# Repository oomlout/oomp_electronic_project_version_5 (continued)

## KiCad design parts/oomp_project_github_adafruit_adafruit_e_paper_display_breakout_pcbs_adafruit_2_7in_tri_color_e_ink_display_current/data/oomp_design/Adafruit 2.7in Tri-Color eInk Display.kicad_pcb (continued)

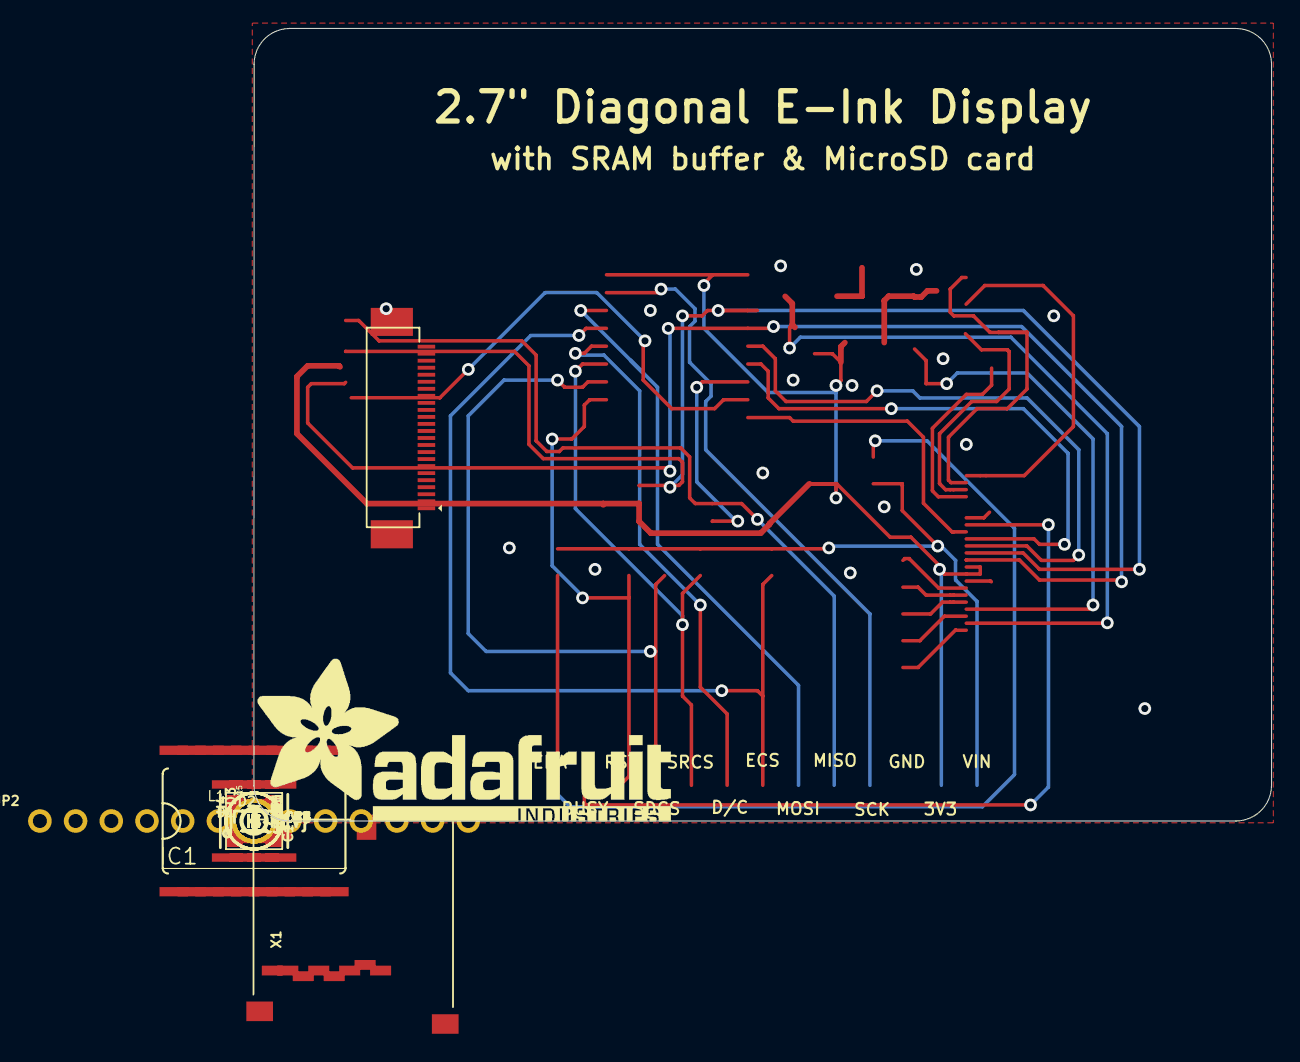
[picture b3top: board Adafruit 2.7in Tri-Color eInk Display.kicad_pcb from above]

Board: 2 copper layers, 72.4 x 56.4 mm, 41 parts (1 on the bottom side), 33 nets.

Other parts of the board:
U$9: PCBFEAT-REV-040
U$39: ADAFRUIT_TEXT_30MM

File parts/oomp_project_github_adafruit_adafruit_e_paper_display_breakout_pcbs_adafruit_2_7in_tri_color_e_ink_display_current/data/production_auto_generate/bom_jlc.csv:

Comment,Designator,Footprint,LCSC Part #
,JP2,Adafruit 2.7in Tri-Color eInk Display-import-fps:1X13_ROUND_70,C2894936
,U$39,Adafruit 2.7in Tri-Color eInk Display-import-fps:ADAFRUIT_TEXT_30MM,
,U$9,Adafruit 2.7in Tri-Color eInk Display-import-fps:PCBFEAT-REV-040,
0.47ohm,R4,Adafruit 2.7in Tri-Color eInk Display-import-fps:0805_10MGAP,
100K,"R1,R2,R3,R5,R6",Adafruit 2.7in Tri-Color eInk Display-import-fps:0805-NO,C149504
10uF/10V+,C15,Adafruit 2.7in Tri-Color eInk Display-import-fps:0805-NO,
10uH,L1,Adafruit 2.7in Tri-Color eInk Display-import-fps:INDUCTOR_4X4MM_NR401,
10µF,"C20,C21",Adafruit 2.7in Tri-Color eInk Display-import-fps:0805-NO,
1uF,"C2,C3,C4,C6,C7,C16,C22,C23,C24",Adafruit 2.7in Tri-Color eInk Display-import-fps:0805-NO,
1uF,C1,Adafruit 2.7in Tri-Color eInk Display-import-fps:0805_10MGAP,
23K256-I/SN,U4,Adafruit 2.7in Tri-Color eInk Display-import-fps:SOIC8_150MIL,
4.7uF/25V,C5,Adafruit 2.7in Tri-Color eInk Display-import-fps:0805-NO,
74HCT245DW,IC1,Adafruit 2.7in Tri-Color eInk Display-import-fps:SO20W,
AP2112K-3.3,U2,Adafruit 2.7in Tri-Color eInk Display-import-fps:SOT23-5,
DNP,R7,Adafruit 2.7in Tri-Color eInk Display-import-fps:0805_10MGAP,
EINK_EPD0231EINK_270IN,EINK1,Adafruit 2.7in Tri-Color eInk Display-import-fps:EINK_270IN,
IRLML0100,Q5,Adafruit 2.7in Tri-Color eInk Display-import-fps:SOT23-3,
MBR0530,"D1,D2,D3",Adafruit 2.7in Tri-Color eInk Display-import-fps:SOD-123,
MICROSD,X1,Adafruit 2.7in Tri-Color eInk Display-import-fps:MICROSD,
